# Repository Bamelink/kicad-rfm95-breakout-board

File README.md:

# KiCad_RFM95_Breakout_Board

## Project Information
This project is a PCB containing the RFM95 868MHz LoRa Chip and a low power STM32L053R8T6 microprocessor.

**CAREFUL:** Neither the schematic, nor the pcb layout has been validated! Please check yourself before using / producing this!

## Things to change for Rev 2.0:
- Make SWD connecter to 2.54mm so Jumpers can fit.
- Get USB to work or better use a USB to UART bridge for Serial communication via USB and programming

## Exporting for JLCPCB
### Generate Files
Open KiCad. In the PCB view, click on File -> Plot -> Generate Drill Files...\
Make sure the Output directory is "gerber/"\
Click on Generate Drill Files and Generate Map files, close the window and click on Plot.\
Then under File -> Fabrication Output -> Footprint Position, check to box to exclude all throughole components and generate the position file.\
In the schematics view, click on Tools -> Generate BOM, select the first option and generate.
### Convert files
JLCPCB uses another header than KiCad. To change the files accordingly, install [this tool](https://github.com/matthewlai/JLCKicadTools) by executing:
```bash
pip install git+https://github.com/matthewlai/JLCKicadTools
```
Move the position file from the geber folder to the main project folder, open a command prompt and execute:
```bash
jlc-kicad-tools .
```
Zip the gerber folder and now you have the new files ready for JLCPCB.

# HINT
The CPW signal trace of the RFM Chip to is set to 50+5% Ohms impedance for FR4 material and 1.6 mm board thickness. The distance between signal and GND top plane is set to 0.2 mm.
Use e.g. [ CPW impedance calulator](https://chemandy.com/calculators/coplanar-waveguide-with-ground-calculator.htm) for calulate the impedance.

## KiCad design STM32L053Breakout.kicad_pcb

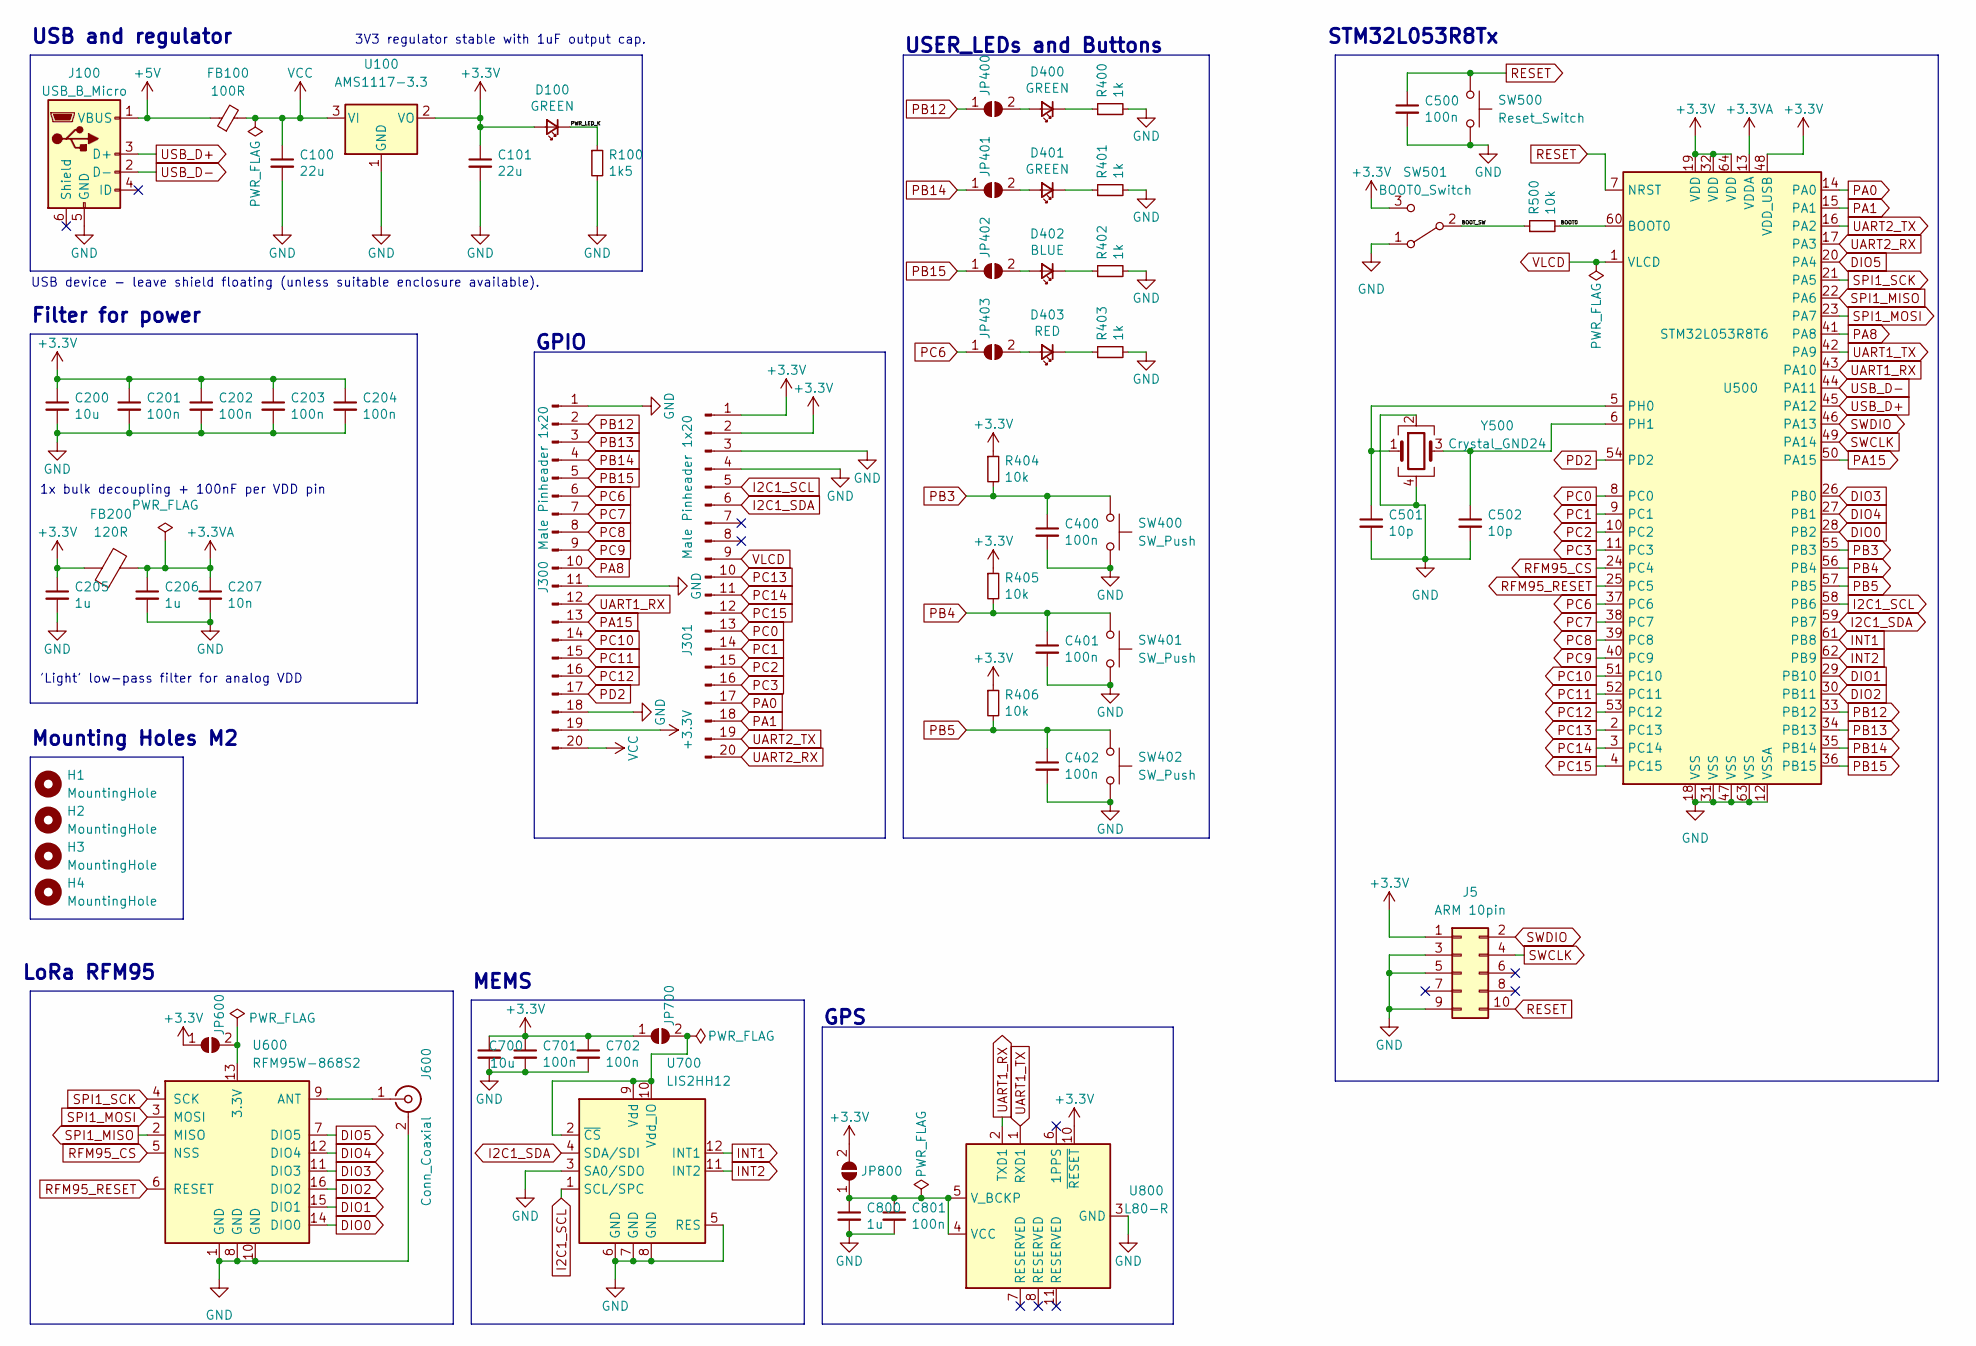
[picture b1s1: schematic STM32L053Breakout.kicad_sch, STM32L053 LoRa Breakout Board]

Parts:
C100, C101: 22u; C_0603_1608Metric; LCSC Part # C59461
C200, C700: 10u; C_0603_1608Metric; LCSC Part # C96446
C201, C202, C203, C204, C400, C401, C402, C500, C701, C702, C801: 100n; C_0402_1005Metric; LCSC Part # C307331
C205, C206, C800: 1u; C_0603_1608Metric; LCSC Part # C15849
C207: 10n; C_0402_1005Metric; LCSC Part # C15195
C501, C502: 10p; C_0402_1005Metric; LCSC Part # C32949
D100, D400, D401: GREEN; LED_0603_1608Metric; LCSC Part # C434420
D402: BLUE; LED_0603_1608Metric; LCSC Part # C375446
D403: RED; LED_0603_1608Metric; LCSC Part # C389517
FB100: 100R; L_0603_1608Metric; LCSC Part # C96995
FB200: 120R; L_0603_1608Metric; LCSC Part # C14709
H1, H2, H3, H4: MountingHole; MountingHole_2.2mm_M2
J5: ARM 10pin; PinHeader_2x05_P1.27mm_Vertical; LCSC Part # C239059
J100: USB_B_Micro; USB_Micro-B_Amphenol_10118194_Horizontal; LCSC Part # C132563
J300, J301: Male Pinheader 1x20; PinHeader_1x20_P2.54mm_Vertical; LCSC Part # C50981
J600: Conn_Coaxial; SMA_Samtec_SMA-J-P-X-ST-EM1_EdgeMount
JP400, JP401, JP402, JP403, JP600, JP700, JP800: SolderJumper_2_Open; SolderJumper-2_P1.3mm_Open_Pad1.0x1.5mm
R100: 1k5; R_0603_1608Metric; LCSC Part # C22843
R400, R401, R402, R403: 1k; R_0603_1608Metric; LCSC Part # C21190
R404, R405, R406, R500: 10k; R_0603_1608Metric; LCSC Part # C25804
SW400, SW401, SW402: SW_Push; SW_SPST_B3U-1000P; LCSC Part # C231329
SW500: Reset_Switch; SW_SPST_B3U-1000P; LCSC Part # C231329
SW501: BOOT0_Switch; SW_E-Switch_EG1224_SPDT_Angled; LCSC Part # C273395
U100: AMS1117-3.3; SOT-223-3_TabPin2; LCSC Part # C6186
U500: STM32L053R8T6; LQFP-64_10x10mm_P0.5mm; LCSC Part # C79207
U600: RFM95W-868S2; HOPERF_RFM9XW_SMD; LCSC Part # C2844472
U700: LIS2HH12; LGA-12_2x2mm_P0.5mm; LCSC Part # C221446
U800: L80-R; Quectel_L80-R; LCSC Part # C133488
Y500: Crystal_GND24; Crystal_SMD_3225-4Pin_3.2x2.5mm; LCSC Part # C112972

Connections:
+3.3V: C101.1, C200.1, C201.1, C202.1, C203.1, C204.1, C205.1, C700.1, C701.1, C702.1, D100.2 (A), FB200.1, J5.1, J300.19, J301.1, J301.2, JP600.1 (A), JP700.1 (A), JP800.2 (B), R404.1, R405.1, R406.1, SW501.3 (C), U100.2 (VO), U500.19 (VDD), U500.32 (VDD), U500.48 (VDD_USB), U500.64 (VDD), U800.10 (~RESET)
+3.3VA: C206.1, C207.1, FB200.2, U500.13 (VDDA)
+5V: FB100.1, J100.1 (VBUS)
/BOOT0: R500.2, U500.60 (BOOT0)
/BOOT_SW: R500.1, SW501.2 (B)
/PWR_LED_K: D100.1 (K), R100.1
DIO0: U500.28 (PB2), U600.14 (DIO0)
DIO1: U500.29 (PB10), U600.15 (DIO1)
DIO2: U500.30 (PB11), U600.16 (DIO2)
DIO3: U500.26 (PB0), U600.11 (DIO3)
DIO4: U500.27 (PB1), U600.12 (DIO4)
DIO5: U500.20 (PA4), U600.7 (DIO5)
GND: C100.2, C101.2, C200.2, C201.2, C202.2, C203.2, C204.2, C205.2, C206.2, C207.2, C400.2, C401.2, C402.2, C500.2, C501.2, C502.2, C700.2, C701.2, C702.2, C800.2, C801.2, J5.3, J5.5, J5.9, J100.5 (GND), J300.1, J300.11, J300.18, J301.3, J301.4, J600.2 (Ext), R100.2, R400.2, R401.2, R402.2, R403.2, SW400.2, SW401.2, SW402.2, SW500.2, SW501.1 (A), U100.1 (GND), U500.12 (VSSA), U500.18 (VSS), U500.31 (VSS), U500.47 (VSS), U500.63 (VSS), U600.1 (GND), U600.8 (GND), U600.10 (GND), U700.3 (SA0/SDO), U700.5 (RES), U700.6 (GND), U700.7 (GND), U700.8 (GND), U800.3 (GND), U800.12 (GND), Y500.2, Y500.4
I2C1_SCL: J301.5, U500.58 (PB6), U700.1 (SCL/SPC)
I2C1_SDA: J301.6, U500.59 (PB7), U700.4 (SDA/SDI)
INT1: U500.61 (PB8), U700.12 (INT1)
INT2: U500.62 (PB9), U700.11 (INT2)
unnamed: C501.1, U500.5 (PH0), Y500.1
unnamed: C502.1, U500.6 (PH1), Y500.3
unnamed: C800.1, C801.1, JP800.1 (A), U800.4 (VCC), U800.5 (V_BCKP)
unnamed: D400.1 (K), R400.1
unnamed: D400.2 (A), JP400.2 (B)
unnamed: D401.1 (K), R401.1
unnamed: D401.2 (A), JP401.2 (B)
unnamed: D402.1 (K), R402.1
unnamed: D402.2 (A), JP402.2 (B)
unnamed: D403.1 (K), R403.1
unnamed: D403.2 (A), JP403.2 (B)
unnamed: J600.1 (In), U600.9 (ANT)
unnamed: JP600.2 (B), U600.13 (3.3V)
unnamed: JP700.2 (B), U700.2 (~CS), U700.9 (Vdd), U700.10 (Vdd_IO)
PA0: J301.17, U500.14 (PA0)
PA1: J301.18, U500.15 (PA1)
PA8: J300.10, U500.41 (PA8)
PA15: J300.13, U500.50 (PA15)
PB3: C400.1, R404.2, SW400.1, U500.55 (PB3)
PB4: C401.1, R405.2, SW401.1, U500.56 (PB4)
PB5: C402.1, R406.2, SW402.1, U500.57 (PB5)
PB12: J300.2, JP400.1 (A), U500.33 (PB12)
PB13: J300.3, U500.34 (PB13)
PB14: J300.4, JP401.1 (A), U500.35 (PB14)
PB15: J300.5, JP402.1 (A), U500.36 (PB15)
PC0: J301.13, U500.8 (PC0)
PC1: J301.14, U500.9 (PC1)
PC2: J301.15, U500.10 (PC2)
PC3: J301.16, U500.11 (PC3)
PC6: J300.6, JP403.1 (A), U500.37 (PC6)
PC7: J300.7, U500.38 (PC7)
PC8: J300.8, U500.39 (PC8)
PC9: J300.9, U500.40 (PC9)
PC10: J300.14, U500.51 (PC10)
PC11: J300.15, U500.52 (PC11)
PC12: J300.16, U500.53 (PC12)
PC13: J301.10, U500.2 (PC13)
PC14: J301.11, U500.3 (PC14)
PC15: J301.12, U500.4 (PC15)
PD2: J300.17, U500.54 (PD2)
RESET: C500.1, J5.10, SW500.1, U500.7 (NRST)
RFM95_CS: U500.24 (PC4), U600.5 (NSS)
RFM95_RESET: U500.25 (PC5), U600.6 (RESET)
SPI1_MISO: U500.22 (PA6), U600.2 (MISO)
SPI1_MOSI: U500.23 (PA7), U600.3 (MOSI)
SPI1_SCK: U500.21 (PA5), U600.4 (SCK)
SWCLK: J5.4, U500.49 (PA14)
SWDIO: J5.2, U500.46 (PA13)
UART1_RX: J300.12, U500.43 (PA10), U800.2 (TXD1)
UART1_TX: U500.42 (PA9), U800.1 (RXD1)
UART2_RX: J301.20, U500.17 (PA3)
UART2_TX: J301.19, U500.16 (PA2)
USB_D+: J100.3 (D+), U500.45 (PA12)
USB_D-: J100.2 (D-), U500.44 (PA11)
VCC: C100.1, FB100.2, J300.20, U100.3 (VI)
VLCD: J301.9, U500.1 (VLCD)

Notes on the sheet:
Mounting Holes M2
STM32L053R8Tx
USB and regulator
MEMS
GPIO
'Light' low-pass filter for analog VDD
1x bulk decoupling + 100nF per VDD pin
USB device - leave shield floating (unless suitable enclosure available).
LoRa RFM95
3V3 regulator stable with 1uF output cap.
Filter for power
GPS
USER_LEDs and Buttons

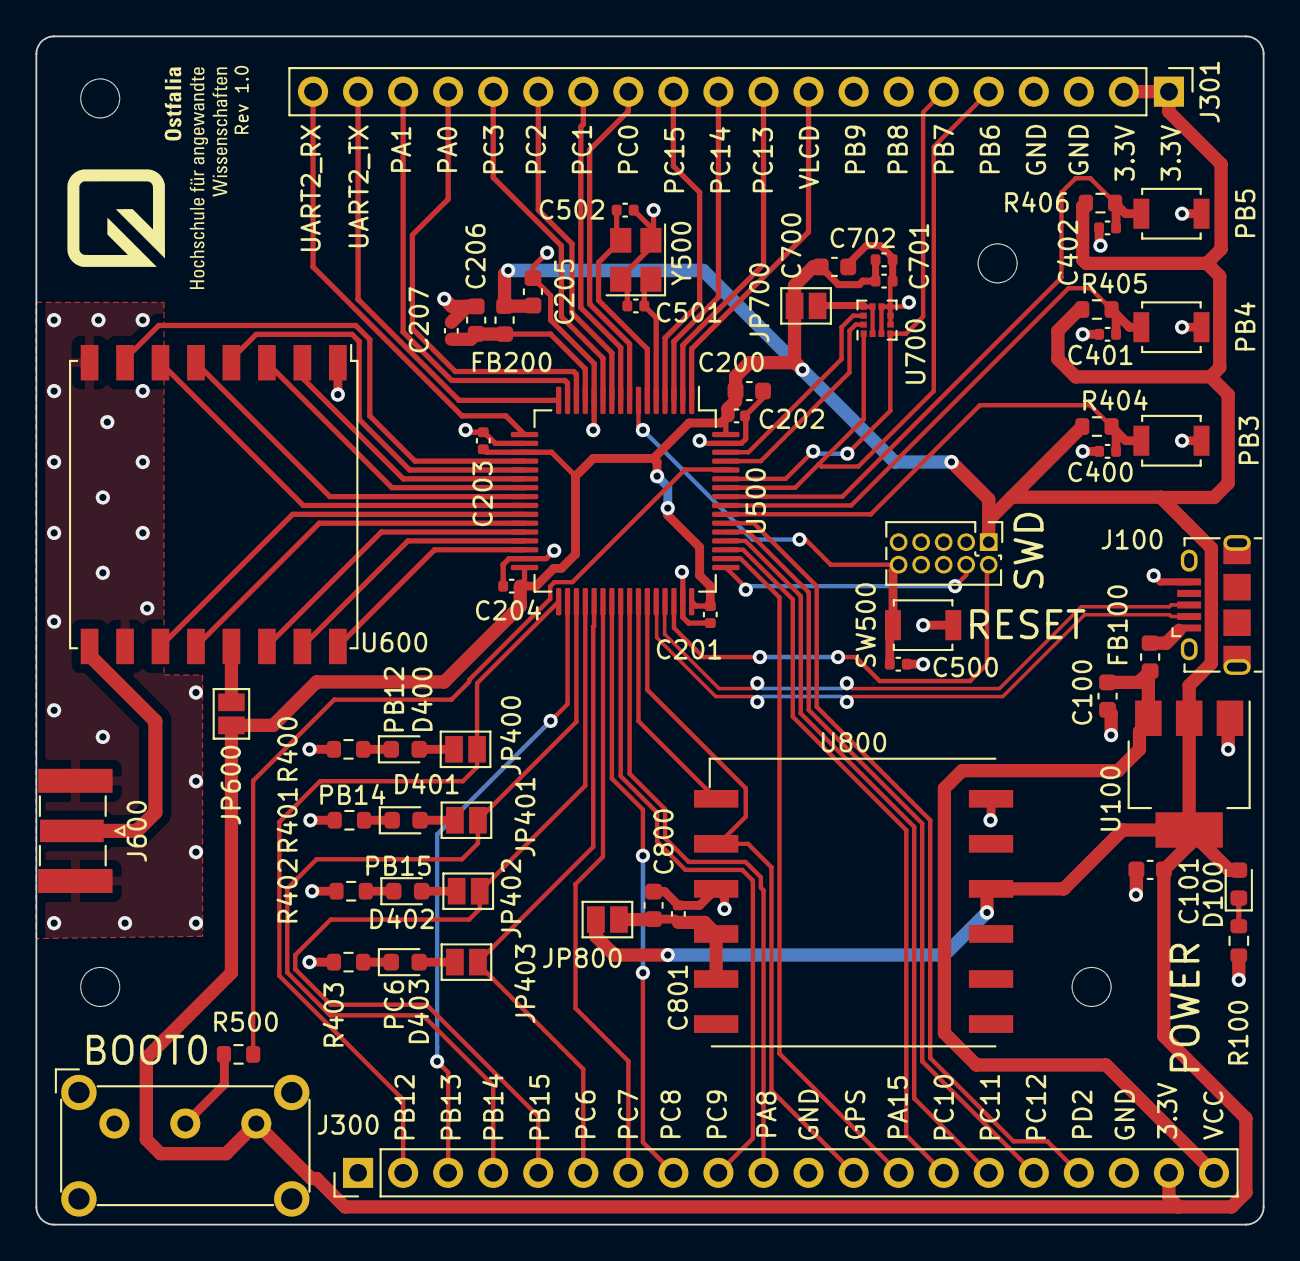
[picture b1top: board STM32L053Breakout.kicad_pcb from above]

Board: 2 copper layers, 69.2 x 67.0 mm, 66 parts (0 on the bottom side), 73 nets.

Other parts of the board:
 : LOGO; ostfalia_logo_5.5mm
 #2: LOGO; ostfalia_logo_schrift_12.5mm

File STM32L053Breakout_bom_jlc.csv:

"Comment","Designator","Footprint","LCSC Part #"
"22u","C100,C101","C_0603_1608Metric","C59461"
"10u","C200,C700","C_0603_1608Metric","C96446"
"100n","C201,C202,C203,C204,C400,C401,C402,C500,C701,C702,C801","C_0402_1005Metric","C307331"
"1u","C205,C206,C800","C_0603_1608Metric","C15849"
"10n","C207","C_0402_1005Metric","C15195"
"10p","C501,C502","C_0402_1005Metric","C32949"
"GREEN","D100,D400,D401","LED_0603_1608Metric","C434420"
"BLUE","D402","LED_0603_1608Metric","C375446"
"RED","D403","LED_0603_1608Metric","C389517"
"100R","FB100","L_0603_1608Metric","C96995"
"120R","FB200","L_0603_1608Metric","C14709"
"ARM 10pin","J5","PinHeader_2x05_P1.27mm_Vertical","C239059"
"USB_B_Micro","J100","USB_Micro-B_Amphenol_10118194_Horizontal","C132563"
"Male Pinheader 1x20","J300,J301","PinHeader_1x20_P2.54mm_Vertical","C50981"
"1k5","R100","R_0603_1608Metric","C22843"
"1k","R400,R401,R402,R403","R_0603_1608Metric","C21190"
"10k","R404,R405,R406,R500","R_0603_1608Metric","C25804"
"SW_Push","SW400,SW401,SW402","SW_SPST_B3U-1000P","C231329"
"Reset_Switch","SW500","SW_SPST_B3U-1000P","C231329"
"BOOT0_Switch","SW501","SW_E-Switch_EG1224_SPDT_Angled","C273395"
"AMS1117-3.3","U100","SOT-223-3_TabPin2","C6186"
"STM32L053R8T6","U500","LQFP-64_10x10mm_P0.5mm","C79207"
"RFM95W-868S2","U600","HOPERF_RFM9XW_SMD","C2844472"
"LIS2HH12","U700","LGA-12_2x2mm_P0.5mm","C221446"
"L80-R","U800","Quectel_L80-R","C133488"
"Crystal_GND24","Y500","Crystal_SMD_3225-4Pin_3.2x2.5mm","C112972"

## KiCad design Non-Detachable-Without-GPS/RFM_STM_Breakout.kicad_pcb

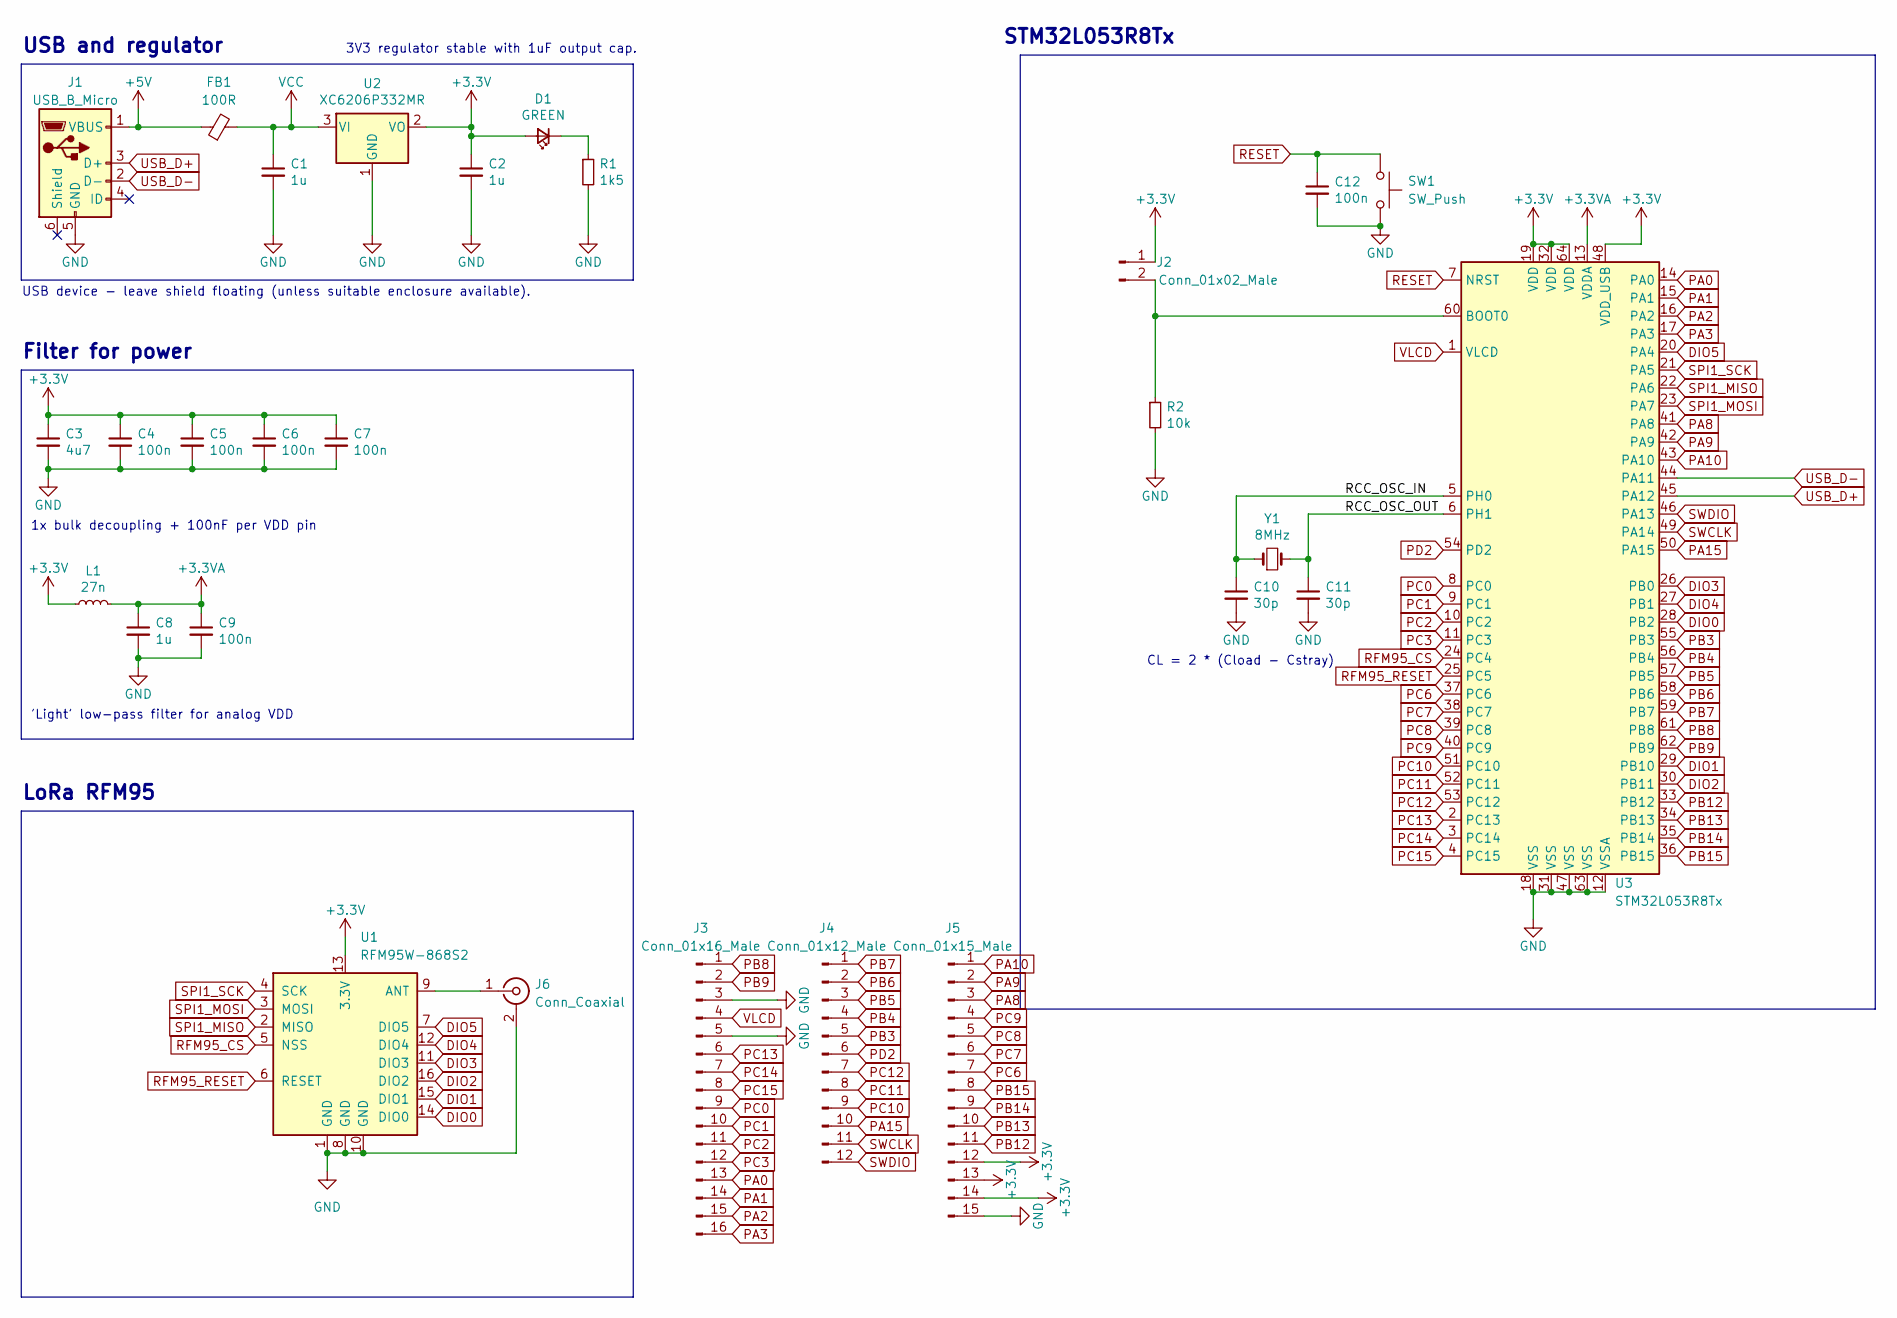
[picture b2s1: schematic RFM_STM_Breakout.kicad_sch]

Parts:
C1, C2: 1u; C_0603_1608Metric; LCSC Part # C15849
C3: 4u7; C_0603_1608Metric; LCSC Part # C19666
C4, C5, C6, C7, C9, C12: 100n; C_0603_1608Metric; LCSC Part # C1525
C8: 1u; C_0603_1608Metric; LCSC Part # C52923
C10, C11: 30p; C_0603_1608Metric; LCSC Part # C1570
D1: GREEN; LED_0603_1608Metric; LCSC Part # C72043
FB1: 100R; L_0805_2012Metric; LCSC Part # C1015
J1: USB_B_Micro; USB_Micro-B_Amphenol_10118194_Horizontal; LCSC Part # C132563
J2: Conn_01x02_Male; PinHeader_1x02_P2.54mm_Vertical; LCSC Part # C492401
J3: Conn_01x16_Male; PinHeader_1x16_P2.54mm_Vertical; LCSC Part # C225268
J4: Conn_01x12_Male; PinHeader_1x12_P2.54mm_Vertical; LCSC Part # C225264
J5: Conn_01x15_Male; PinHeader_1x15_P2.54mm_Vertical; LCSC Part # C124373
J6: Conn_Coaxial; SMA_Samtec_SMA-J-P-X-ST-EM1_EdgeMount
L1: 27n; L_0402_1005Metric; LCSC Part # C18830
R1: 1k5; R_0603_1608Metric; LCSC Part # C22842
R2: 10k; R_0603_1608Metric; LCSC Part # C25744
SW1: SW_Push; SW_SPST_B3U-1000P; LCSC Part # C231329
U1: RFM95W-868S2; HOPERF_RFM9XW_SMD; LCSC Part # C2844472
U2: XC6206P332MR; SOT-23; LCSC Part # C5446
U3: STM32L053R8Tx; LQFP-64_10x10mm_P0.5mm; LCSC Part # C79207
Y1: 8MHz; Crystal_SMD_5032-2Pin_5.0x3.2mm; LCSC Part # C115962

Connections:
+3.3V: C2.1, C3.1, C4.1, C5.1, C6.1, C7.1, D1.2 (A), J2.1, J5.12, J5.13, J5.14, L1.1, U1.13 (3.3V), U2.2 (VO), U3.19 (VDD), U3.32 (VDD), U3.48 (VDD_USB), U3.64 (VDD)
+3.3VA: C8.1, C9.1, L1.2, U3.13 (VDDA)
+5V: FB1.1, J1.1 (VBUS)
/RCC_OSC_IN: C10.1, U3.5 (PH0), Y1.1
/RCC_OSC_OUT: C11.1, U3.6 (PH1), Y1.2
DIO0: U1.14 (DIO0), U3.28 (PB2)
DIO1: U1.15 (DIO1), U3.29 (PB10)
DIO2: U1.16 (DIO2), U3.30 (PB11)
DIO3: U1.11 (DIO3), U3.26 (PB0)
DIO4: U1.12 (DIO4), U3.27 (PB1)
DIO5: U1.7 (DIO5), U3.20 (PA4)
GND: C1.2, C2.2, C3.2, C4.2, C5.2, C6.2, C7.2, C8.2, C9.2, C10.2, C11.2, C12.2, J1.5 (GND), J3.3, J3.5, J5.15, J6.2 (Ext), R1.2, R2.2, SW1.2, U1.1 (GND), U1.8 (GND), U1.10 (GND), U2.1 (GND), U3.12 (VSSA), U3.18 (VSS), U3.31 (VSS), U3.47 (VSS), U3.63 (VSS)
unnamed: D1.1 (K), R1.1
unnamed: J2.2, R2.1, U3.60 (BOOT0)
unnamed: J6.1 (In), U1.9 (ANT)
PA0: J3.13, U3.14 (PA0)
PA1: J3.14, U3.15 (PA1)
PA2: J3.15, U3.16 (PA2)
PA3: J3.16, U3.17 (PA3)
PA8: J5.3, U3.41 (PA8)
PA9: J5.2, U3.42 (PA9)
PA10: J5.1, U3.43 (PA10)
PA15: J4.10, U3.50 (PA15)
PB3: J4.5, U3.55 (PB3)
PB4: J4.4, U3.56 (PB4)
PB5: J4.3, U3.57 (PB5)
PB6: J4.2, U3.58 (PB6)
PB7: J4.1, U3.59 (PB7)
PB8: J3.1, U3.61 (PB8)
PB9: J3.2, U3.62 (PB9)
PB12: J5.11, U3.33 (PB12)
PB13: J5.10, U3.34 (PB13)
PB14: J5.9, U3.35 (PB14)
PB15: J5.8, U3.36 (PB15)
PC0: J3.9, U3.8 (PC0)
PC1: J3.10, U3.9 (PC1)
PC2: J3.11, U3.10 (PC2)
PC3: J3.12, U3.11 (PC3)
PC6: J5.7, U3.37 (PC6)
PC7: J5.6, U3.38 (PC7)
PC8: J5.5, U3.39 (PC8)
PC9: J5.4, U3.40 (PC9)
PC10: J4.9, U3.51 (PC10)
PC11: J4.8, U3.52 (PC11)
PC12: J4.7, U3.53 (PC12)
PC13: J3.6, U3.2 (PC13)
PC14: J3.7, U3.3 (PC14)
PC15: J3.8, U3.4 (PC15)
PD2: J4.6, U3.54 (PD2)
RESET: C12.1, SW1.1, U3.7 (NRST)
RFM95_CS: U1.5 (NSS), U3.24 (PC4)
RFM95_RESET: U1.6 (RESET), U3.25 (PC5)
SPI1_MISO: U1.2 (MISO), U3.22 (PA6)
SPI1_MOSI: U1.3 (MOSI), U3.23 (PA7)
SPI1_SCK: U1.4 (SCK), U3.21 (PA5)
SWCLK: J4.11, U3.49 (PA14)
SWDIO: J4.12, U3.46 (PA13)
USB_D+: J1.3 (D+), U3.45 (PA12)
USB_D-: J1.2 (D-), U3.44 (PA11)
VCC: C1.1, FB1.2, U2.3 (VI)
VLCD: J3.4, U3.1 (VLCD)

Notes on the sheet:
1x bulk decoupling + 100nF per VDD pin
LoRa RFM95
USB device - leave shield floating (unless suitable enclosure available).
'Light' low-pass filter for analog VDD
USB and regulator
STM32L053R8Tx
Filter for power
CL = 2 * (Cload - Cstray)
3V3 regulator stable with 1uF output cap.

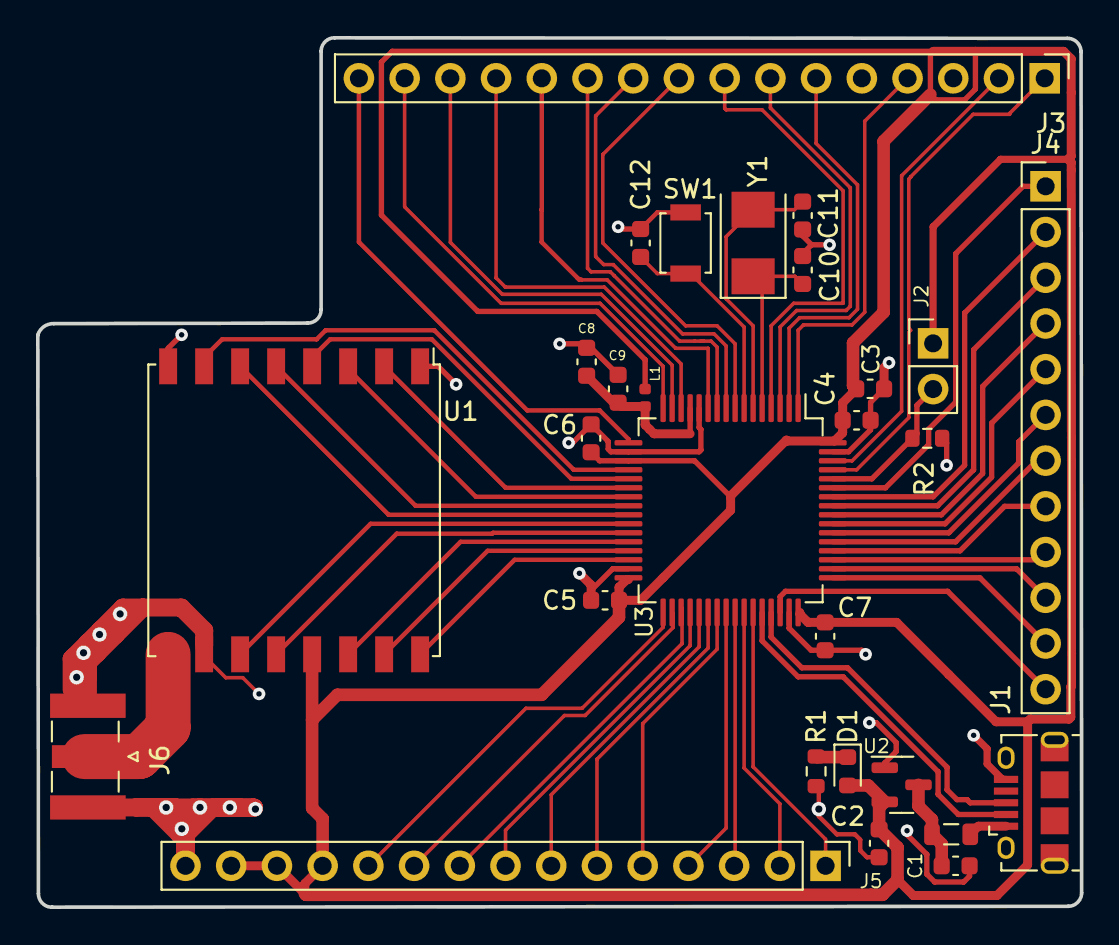
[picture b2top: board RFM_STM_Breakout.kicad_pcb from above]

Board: 2 copper layers, 58.0 x 48.3 mm, 28 parts (0 on the bottom side), 61 nets.

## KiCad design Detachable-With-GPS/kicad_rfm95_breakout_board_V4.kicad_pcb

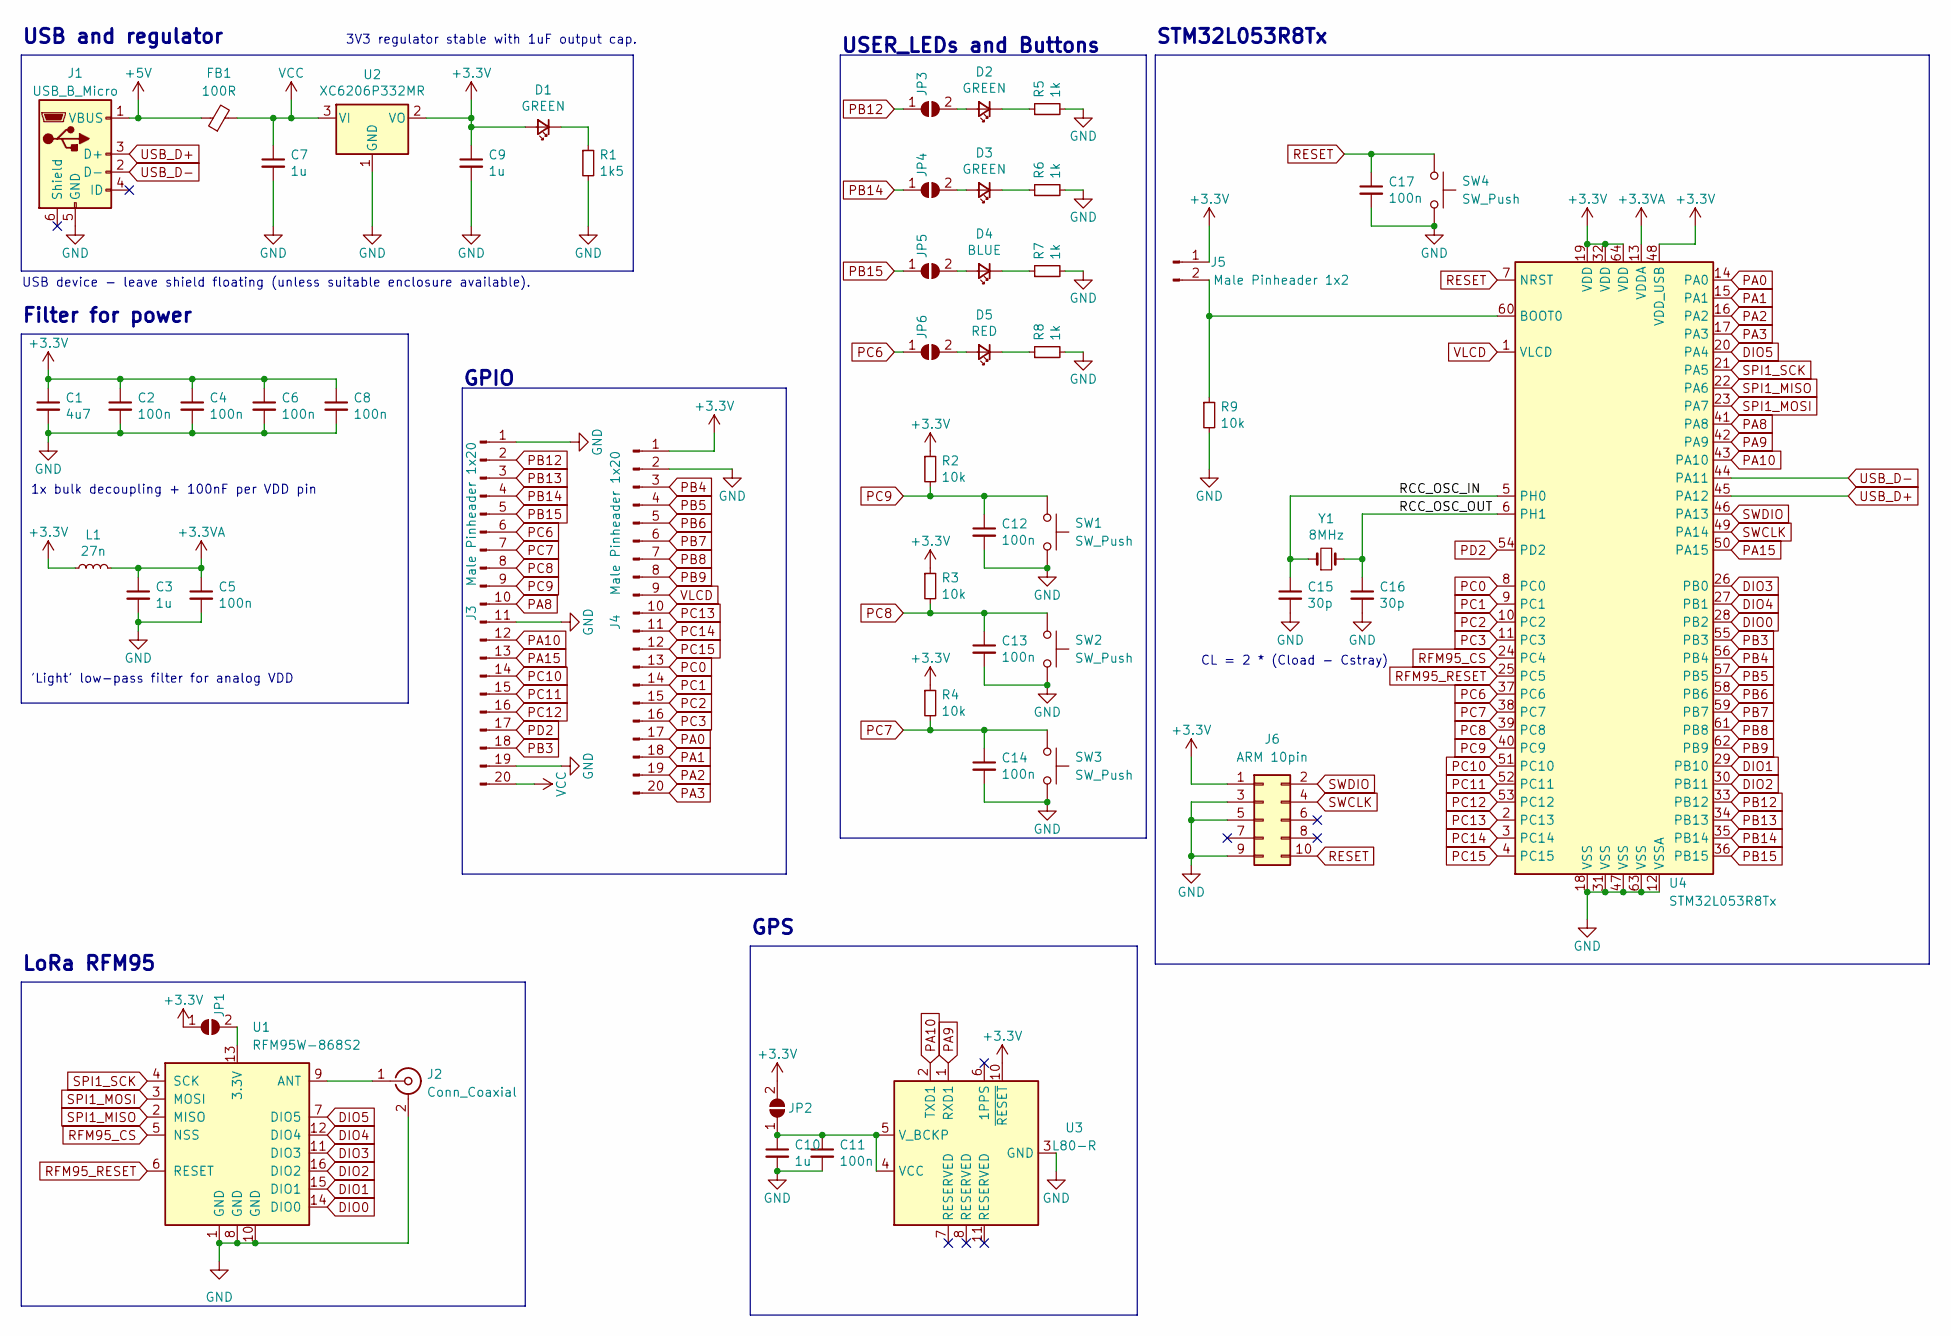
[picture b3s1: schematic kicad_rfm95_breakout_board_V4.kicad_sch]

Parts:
C1: 4u7; C_0603_1608Metric; LCSC Part # C19666
C2, C4, C5, C6, C8, C11, C12, C13, C14, C17: 100n; C_0603_1608Metric; LCSC Part # C1525
C3, C10: 1u; C_0603_1608Metric; LCSC Part # C52923
C7, C9: 1u; C_0603_1608Metric; LCSC Part # C15849
C15, C16: 30p; C_0603_1608Metric; LCSC Part # C1570
D1: GREEN; LED_0603_1608Metric; LCSC Part # C72043
D2, D3: GREEN; LED_0603_1608Metric; LCSC Part # C72041
D4: BLUE; LED_0603_1608Metric; LCSC Part # C72041
D5: RED; LED_0603_1608Metric; LCSC Part # C72041
FB1: 100R; L_0805_2012Metric; LCSC Part # C1015
J1: USB_B_Micro; USB_Micro-B_Amphenol_10118194_Horizontal; LCSC Part # C132563
J2: Conn_Coaxial; SMA_Samtec_SMA-J-P-X-ST-EM1_EdgeMount
J3, J4: Male Pinheader 1x20; PinHeader_1x20_P2.54mm_Vertical; LCSC Part # C50981
J5: Male Pinheader 1x2; PinHeader_1x02_P2.54mm_Vertical; LCSC Part # C492401
J6: ARM 10pin; PinHeader_2x05_P1.27mm_Vertical
JP1, JP2, JP3, JP4, JP5, JP6: SolderJumper_2_Open; SolderJumper-2_P1.3mm_Open_Pad1.0x1.5mm
L1: 27n; L_0402_1005Metric; LCSC Part # C18830
R1: 1k5; R_0603_1608Metric; LCSC Part # C22842
R2, R3, R4, R9: 10k; R_0603_1608Metric; LCSC Part # C25744
R5, R6, R7, R8: 1k; R_0603_1608Metric; LCSC Part # C22843
SW1, SW2, SW3, SW4: SW_Push; SW_SPST_B3U-1000P; LCSC Part # C231329
U1: RFM95W-868S2; HOPERF_RFM9XW_SMD; LCSC Part # C2844472
U2: XC6206P332MR; SOT-23; LCSC Part # C5446
U3: L80-R; Quectel_L80-R; LCSC Part # C188357
U4: STM32L053R8Tx; LQFP-64_10x10mm_P0.5mm; LCSC Part # C79207
Y1: 8MHz; Crystal_SMD_5032-2Pin_5.0x3.2mm; LCSC Part # C115962

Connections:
+3.3V: C1.1, C2.1, C4.1, C6.1, C8.1, C9.1, D1.2 (A), J4.1, J5.1, J6.1, JP1.1 (A), JP2.2 (B), L1.1, R2.1, R3.1, R4.1, U2.2 (VO), U3.10 (~RESET), U4.19 (VDD), U4.32 (VDD), U4.48 (VDD_USB), U4.64 (VDD)
+3.3VA: C3.1, C5.1, L1.2, U4.13 (VDDA)
+5V: FB1.1, J1.1 (VBUS)
/RCC_OSC_IN: C15.1, U4.5 (PH0), Y1.1
/RCC_OSC_OUT: C16.1, U4.6 (PH1), Y1.2
DIO0: U1.14 (DIO0), U4.28 (PB2)
DIO1: U1.15 (DIO1), U4.29 (PB10)
DIO2: U1.16 (DIO2), U4.30 (PB11)
DIO3: U1.11 (DIO3), U4.26 (PB0)
DIO4: U1.12 (DIO4), U4.27 (PB1)
DIO5: U1.7 (DIO5), U4.20 (PA4)
GND: C1.2, C2.2, C3.2, C4.2, C5.2, C6.2, C7.2, C8.2, C9.2, C10.2, C11.2, C12.2, C13.2, C14.2, C15.2, C16.2, C17.2, J1.5 (GND), J2.2 (Ext), J3.1, J3.11, J3.19, J4.2, J6.3, J6.5, J6.9, R1.2, R5.2, R6.2, R7.2, R8.2, R9.2, SW1.2, SW2.2, SW3.2, SW4.2, U1.1 (GND), U1.8 (GND), U1.10 (GND), U2.1 (GND), U3.3 (GND), U3.12 (GND), U4.12 (VSSA), U4.18 (VSS), U4.31 (VSS), U4.47 (VSS), U4.63 (VSS)
unnamed: C10.1, C11.1, JP2.1 (A), U3.4 (VCC), U3.5 (V_BCKP)
unnamed: D1.1 (K), R1.1
unnamed: D2.1 (K), R5.1
unnamed: D2.2 (A), JP3.2 (B)
unnamed: D3.1 (K), R6.1
unnamed: D3.2 (A), JP4.2 (B)
unnamed: D4.1 (K), R7.1
unnamed: D4.2 (A), JP5.2 (B)
unnamed: D5.1 (K), R8.1
unnamed: D5.2 (A), JP6.2 (B)
unnamed: J2.1 (In), U1.9 (ANT)
unnamed: J5.2, R9.1, U4.60 (BOOT0)
unnamed: JP1.2 (B), U1.13 (3.3V)
PA0: J4.17, U4.14 (PA0)
PA1: J4.18, U4.15 (PA1)
PA2: J4.19, U4.16 (PA2)
PA3: J4.20, U4.17 (PA3)
PA8: J3.10, U4.41 (PA8)
PA9: U3.1 (RXD1), U4.42 (PA9)
PA10: J3.12, U3.2 (TXD1), U4.43 (PA10)
PA15: J3.13, U4.50 (PA15)
PB3: J3.18, U4.55 (PB3)
PB4: J4.3, U4.56 (PB4)
PB5: J4.4, U4.57 (PB5)
PB6: J4.5, U4.58 (PB6)
PB7: J4.6, U4.59 (PB7)
PB8: J4.7, U4.61 (PB8)
PB9: J4.8, U4.62 (PB9)
PB12: J3.2, JP3.1 (A), U4.33 (PB12)
PB13: J3.3, U4.34 (PB13)
PB14: J3.4, JP4.1 (A), U4.35 (PB14)
PB15: J3.5, JP5.1 (A), U4.36 (PB15)
PC0: J4.13, U4.8 (PC0)
PC1: J4.14, U4.9 (PC1)
PC2: J4.15, U4.10 (PC2)
PC3: J4.16, U4.11 (PC3)
PC6: J3.6, JP6.1 (A), U4.37 (PC6)
PC7: C14.1, J3.7, R4.2, SW3.1, U4.38 (PC7)
PC8: C13.1, J3.8, R3.2, SW2.1, U4.39 (PC8)
PC9: C12.1, J3.9, R2.2, SW1.1, U4.40 (PC9)
PC10: J3.14, U4.51 (PC10)
PC11: J3.15, U4.52 (PC11)
PC12: J3.16, U4.53 (PC12)
PC13: J4.10, U4.2 (PC13)
PC14: J4.11, U4.3 (PC14)
PC15: J4.12, U4.4 (PC15)
PD2: J3.17, U4.54 (PD2)
RESET: C17.1, J6.10, SW4.1, U4.7 (NRST)
RFM95_CS: U1.5 (NSS), U4.24 (PC4)
RFM95_RESET: U1.6 (RESET), U4.25 (PC5)
SPI1_MISO: U1.2 (MISO), U4.22 (PA6)
SPI1_MOSI: U1.3 (MOSI), U4.23 (PA7)
SPI1_SCK: U1.4 (SCK), U4.21 (PA5)
SWCLK: J6.4, U4.49 (PA14)
SWDIO: J6.2, U4.46 (PA13)
USB_D+: J1.3 (D+), U4.45 (PA12)
USB_D-: J1.2 (D-), U4.44 (PA11)
VCC: C7.1, FB1.2, J3.20, U2.3 (VI)
VLCD: J4.9, U4.1 (VLCD)

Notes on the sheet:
GPS
CL = 2 * (Cload - Cstray)
3V3 regulator stable with 1uF output cap.
Filter for power
USB and regulator
1x bulk decoupling + 100nF per VDD pin
LoRa RFM95
USER_LEDs and Buttons
'Light' low-pass filter for analog VDD
STM32L053R8Tx
USB device - leave shield floating (unless suitable enclosure available).
GPIO

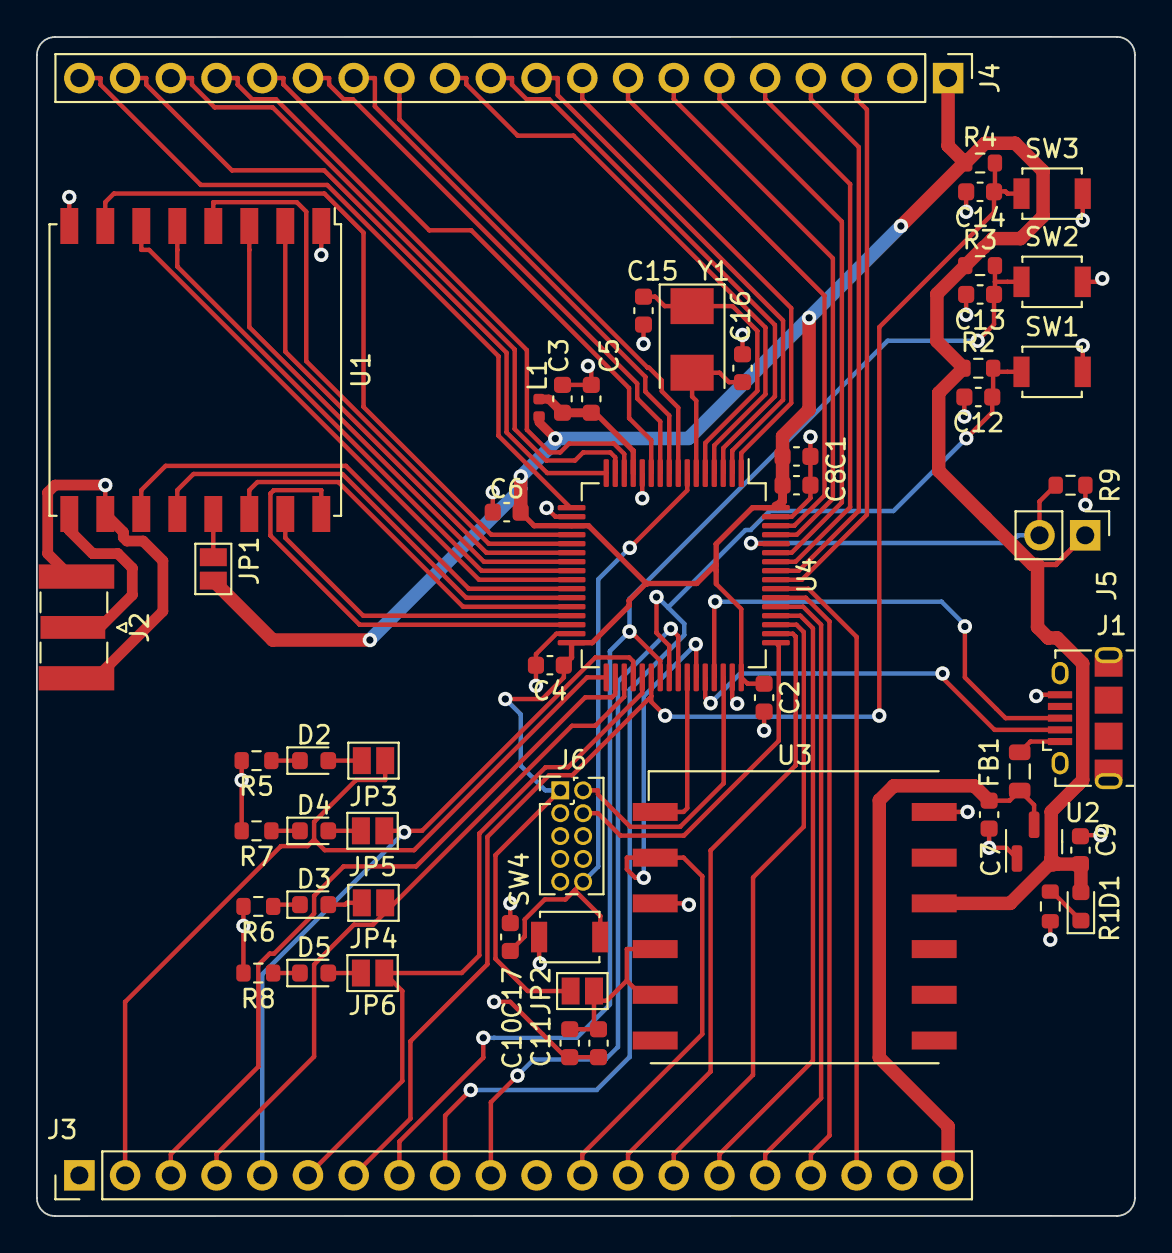
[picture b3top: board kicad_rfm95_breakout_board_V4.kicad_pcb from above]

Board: 2 copper layers, 61.0 x 65.5 mm, 54 parts (0 on the bottom side), 71 nets.

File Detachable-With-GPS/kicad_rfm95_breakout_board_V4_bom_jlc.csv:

"Comment","Designator","Footprint","LCSC Part #"
"4u7","C1","C_0603_1608Metric","C19666"
"100n","C2,C4,C5,C6,C8,C11,C12,C13,C14,C17","C_0603_1608Metric","C1525"
"1u","C3,C10","C_0603_1608Metric","C52923"
"1u","C7,C9","C_0603_1608Metric","C15849"
"30p","C15,C16","C_0603_1608Metric","C1570"
"GREEN","D1","LED_0603_1608Metric","C72043"
"GREEN","D2,D3","LED_0603_1608Metric","C72041"
"BLUE","D4","LED_0603_1608Metric","C72041"
"RED","D5","LED_0603_1608Metric","C72041"
"100R","FB1","L_0805_2012Metric","C1015"
"USB_B_Micro","J1","USB_Micro-B_Amphenol_10118194_Horizontal","C132563"
"Male Pinheader 1x20","J3,J4","PinHeader_1x20_P2.54mm_Vertical","C50981"
"Male Pinheader 1x2","J5","PinHeader_1x02_P2.54mm_Vertical","C492401"
"27n","L1","L_0402_1005Metric","C18830"
"1k5","R1,R10","R_0603_1608Metric","C22842"
"10k","R2,R3,R4,R9","R_0603_1608Metric","C25744"
"1k","R5,R6,R7,R8","R_0603_1608Metric","C22843"
"SW_Push","SW1,SW2,SW3,SW4","SW_SPST_B3U-1000P","C231329"
"RFM95W-868S2","U1","HOPERF_RFM9XW_SMD","C2844472"
"XC6206P332MR","U2","SOT-23","C5446"
"L80-R","U3","Quectel_L80-R","C188357"
"STM32L053R8Tx","U4","LQFP-64_10x10mm_P0.5mm","C79207"
"8MHz","Y1","Crystal_SMD_5032-2Pin_5.0x3.2mm","C115962"

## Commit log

2022-06-28 Useful readme
2022-06-28 Remove Top GND Layer
2022-06-28 Change angles and 3.3V Rail
2022-06-28 impedance adjustment of the signal trace, improve GND conncetion, fix board border
2022-07-05 Detachtable with GPS
2022-07-05 Remove old
2022-07-05 Update USB Pullup (R already internal in STM32L0 processors)
2022-07-06 Improvement
2022-07-09 add rfm signal out to CPW & add Logos
2022-07-10 Change Keepout and add 3.3V Rail to RFM
2022-07-10 Add missing netlist
2022-07-26 Add sensor and change bom for GPS
2022-07-30 Add mems
2022-08-06 Change BOM for JLC
2022-08-08 Add Rev Number
